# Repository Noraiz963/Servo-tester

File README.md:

# Servo Motor Tester

A simple 555-timer-based servo tester designed in KiCad — generates a variable-width pulse signal to manually test and center RC servo motors without needing a microcontroller or transmitter.

## Circuit Overview

- **Pulse generator**: NE555P timer IC (U1) configured to output a PWM-style signal on the SIGNAL pin
- **Pulse width adjustment**: Potentiometer (RV1) lets you sweep the servo across its range by hand
- **Timing components**: Resistors (R2, R3) and capacitor (C1, 22nF) set the timer's frequency and pulse characteristics
- **Reverse polarity protection**: Diode (D1, 1N4148) on the power input
- **Power indicator**: LED (D2) with current-limiting resistor (R1), lit whenever the board is powered
- **Output connector**: 3-pin header (J1) for Signal / Vcc / GND, matching standard servo connector pinout
- **Input connector**: 2-pin header (J2) for DC power input

## Schematic

## PCB Layout

## 3D Render

## Bill of Materials

| Ref | Component | Value |
|-----|-----------|-------|
| U1 | Timer IC | NE555P |
| RV1 | Potentiometer | — |
| R1 | Resistor | 1kΩ |
| R2 | Resistor | — |
| R3 | Resistor | 56kΩ |
| C1 | Capacitor | 22nF |
| D1 | Diode | 1N4148 |
| D2 | LED | Power indicator |
| J1 | Header (3-pin) | Signal / Vcc / GND (servo output) |
| J2 | Header (2-pin) | DC input |

## Tools Used

- KiCad 10.0 (schematic capture, PCB layout, 3D visualization)

## Status

Completed — third PCB design project, first design built around an active timing IC (NE555) rather than passive rectification/regulation only.

## Notes

Built as a learning project to practice designing around a general-purpose timer IC and generating a controllable output signal, following on from the two power-supply-focused boards in this series.

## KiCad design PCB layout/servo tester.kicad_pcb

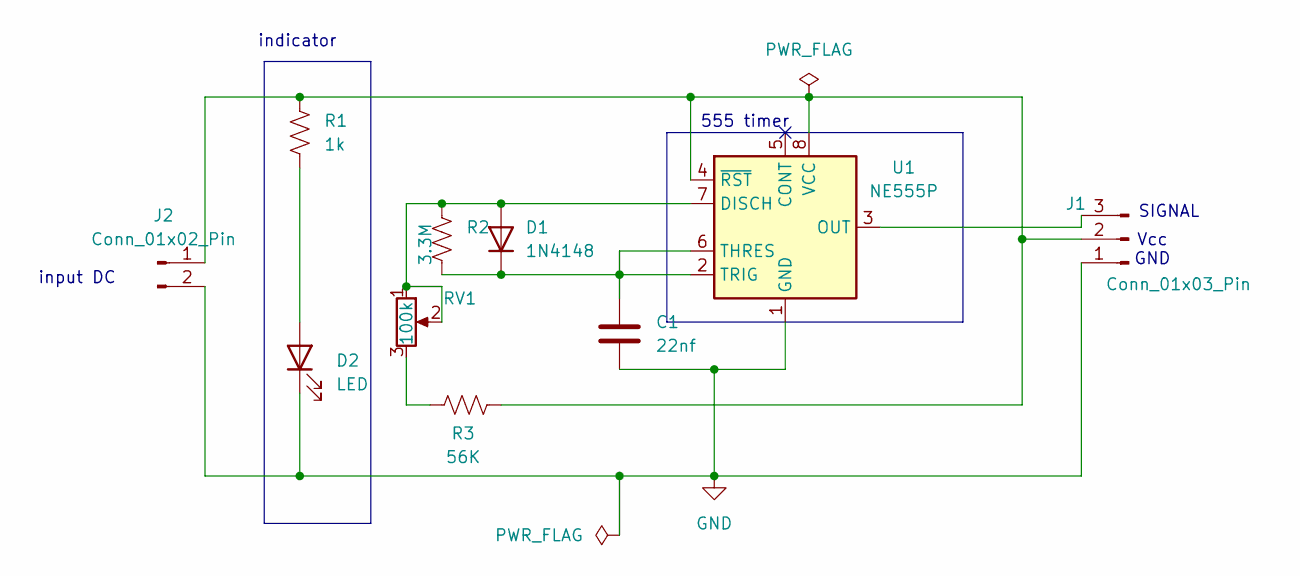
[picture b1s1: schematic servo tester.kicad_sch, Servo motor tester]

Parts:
C1: 22nf; C_Disc_D4.3mm_W1.9mm_P5.00mm
D1: 1N4148; D_DO-35_SOD27_P7.62mm_Horizontal
D2: LED; LED_D3.0mm
J1: Conn_01x03_Pin; PinHeader_1x03_P2.54mm_Horizontal
J2: Conn_01x02_Pin; PinHeader_1x02_P2.54mm_Horizontal
R1: 1k; R_Axial_DIN0204_L3.6mm_D1.6mm_P7.62mm_Horizontal
R2: 3.3M; R_Axial_DIN0204_L3.6mm_D1.6mm_P7.62mm_Horizontal
R3: 56K; R_Axial_DIN0204_L3.6mm_D1.6mm_P7.62mm_Horizontal
RV1: 100k; Potentiometer_Alps_RK163_Single_Horizontal
U1: NE555P; DIP-8_W7.62mm

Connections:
GND: C1.2, D2.1 (K), J1.1, J2.2, U1.1 (GND)
unnamed: D1.2 (A), R2.1, RV1.1, RV1.2, U1.7 (DISCH)
unnamed: C1.1, D1.1 (K), R2.2, U1.2 (TRIG), U1.6 (THRES)
unnamed: D2.2 (A), R1.2
unnamed: J1.2, J2.1, R1.1, R3.1, U1.4 (~RST), U1.8 (VCC)
unnamed: J1.3, U1.3 (OUT)
unnamed: R3.2, RV1.3

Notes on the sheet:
indicator
GND
input DC
Vcc
SIGNAL
555 timer

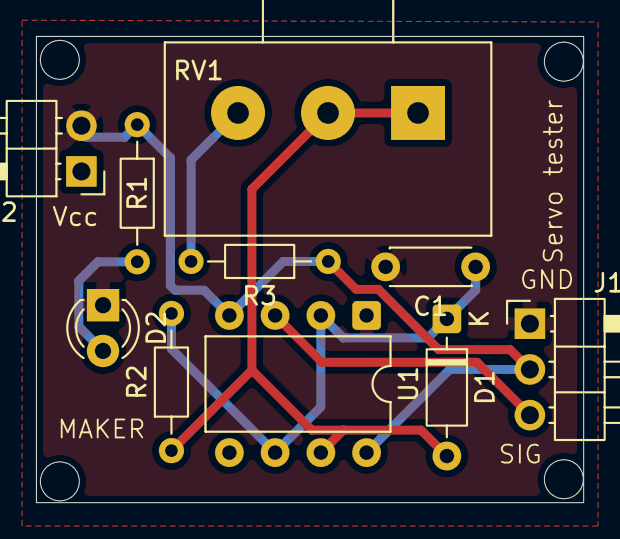
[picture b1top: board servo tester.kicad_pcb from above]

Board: 2 copper layers, 30.4 x 25.9 mm, 10 parts (0 on the bottom side), 7 nets.
